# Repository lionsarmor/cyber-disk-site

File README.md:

# RODDY Cyber Disk inspector

Website: http://disk.roddy.world/

GitHub Pages: https://lionsarmor.github.io/cyber-disk-site/ (redirects to the custom domain).

Hardware R3 publication: five routed PCBs with actual RODDY silkscreen, separate KiCad/schematic/Gerber downloads, supplier-grouped BOM, Drive R5 mechanism and External Case R4 with Daughterboard R3. The development repository remains private.

Saved-file ERC, DRC and independent pin-map checks pass with zero unrouted connections. These are prototype files: printed/powered sample qualification and real-host emulation testing remain required. Firmware is unchanged in this hardware publication.

GitHub Actions deploys `site/` to GitHub Pages on each push to main. DNS: CNAME `disk` points to `lionsarmor.github.io`. All asset URLs are relative. Obsolete generated geometry has been removed from the current deployment; historical revisions remain in Git.

Start with `?model=pcb%2Fdock&view=b&v=hardware-r3` for the branded PCB underside, `?model=drive%2Fmotion&v=hardware-r3` for the mechanism, or `?model=external%2Fservice&v=hardware-r3` for internal wiring. Board files are at `boards.html`; verification details are at `electrical.html`.

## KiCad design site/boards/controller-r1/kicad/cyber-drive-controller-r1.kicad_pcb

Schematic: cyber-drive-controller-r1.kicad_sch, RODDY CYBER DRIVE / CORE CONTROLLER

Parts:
A1: PICO 2 SC1632 SOCKETED; Controller_A1
C1: 47uF 16V; Controller_C1
C2: 100nF 50V; Controller_C2
C3: 100nF 50V; Controller_C3
C5: 100nF 50V; Controller_C5
C6: 22uF 16V / OUTPUT; Controller_C6
C7: 100nF 50V; Controller_C7
C9: 1uF 50V X7R; Controller_C9
C10: 22nF AUDIO LP1; Controller_C10
C11: 22nF AUDIO LP2; Controller_C11
C12: 100nF AUDIO COUPLING; Controller_C12
C13: 100uF 16V / SPEAKER DC BLOCK; Controller_C13
C14: 47uF 16V / AMP RESERVOIR; Controller_C14
C15: 100nF AMP DECOUPLING; Controller_C15
C16: 100nF AUDIO STABILITY; Controller_C16
C17: 22uF 16V / AMP BYPASS; Controller_C17
D1: 1N5819 / USB BACKFEED BLOCK; Controller_D1
F1: 2A FAST / LOW DROP; Controller_F1
J1: 34-PIN PC FLOPPY; Controller_J1
J2: FLOPPY POWER 5V GND GND 12V; Controller_J2
J3: 1725708 / CONTACT WIRES 1 TO 7; Controller_J3
J4: DOCK LINK 3V3 UART; Controller_J4
J5: 3V3 OUT / INTERLOCK RETURN; Controller_J5
J6: SPEAKER 8 OHM / + GND; Controller_J6
Q1: IRLZ44N / HARD DISCHARGE; Controller_Q1
Q2: TN0702 / ARM PERMISSION; Controller_Q2
Q3: TN0702 / INTERLOCK PERMISSION; Controller_Q3
Q4: TN0702 / FDD INDEX; Controller_Q4
Q5: TN0702 / FDD TRK0; Controller_Q5
Q6: TN0702 / FDD WP; Controller_Q6
Q7: TN0702 / FDD RDATA; Controller_Q7
Q8: TN0702 / FDD CHANGE; Controller_Q8
Q9: SUP53P06 / MEDIA INPUT CUT; Controller_Q9
Q10: TN0702 / OE ARM; Controller_Q10
Q11: TN0702 / OE INTERLOCK; Controller_Q11
R1: 10k SPI CS DEFAULT; Controller_R1
R2: 10k MEDIA ERROR PULLUP; Controller_R2
R4: 15k 1%; Controller_R4
R5: 10k 1%; Controller_R5
R6: 68R FAILSAFE BLEED; Controller_R6
R7: 680R DEFAULT OFF; Controller_R7
R8: 2R2 DISCHARGE; Controller_R8
R9: 10k MISO DEFAULT; Controller_R9
R10: 1 OHM CAP ESR; Controller_R10
R11: 2k2 ARM GATE; Controller_R11
R12: 2k2 INTERLOCK GATE; Controller_R12
R13: 10k OE DEFAULT OFF; Controller_R13
R14: 47k AUDIO ATTENUATOR; Controller_R14
R15: 2k2 AUDIO BIAS; Controller_R15
R16: 2k2 AUDIO FILTER; Controller_R16
R17: 10R AUDIO STABILITY; Controller_R17
RN1: 8x10k BUSSED / COMMON PIN1; Controller_RN1
RN2: 8x10k BUSSED / COMMON PIN1; Controller_RN2
RN3: 8x1k BUSSED / COMMON GND; Controller_RN3
U1: SN74LVC245AN / 5V-TOL INPUT; Controller_U1
U2: SN74LVC245AN / 5V-TOL INPUT; Controller_U2
U4: SN74LVC245AN / SWITCHED MEDIA ISOLATION; Controller_U4
U6: LP2951ACN / SWITCHED 3V1 100mA; Controller_U6
U7: LM386N-1 / SAMPLE AUDIO; Controller_U7

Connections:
AMP_BYPASS: C17.1 (AMP_BYPASS), U7.7 (AMP_BYPASS)
AMP_OUT: C13.1 (AMP_OUT), C16.1 (AMP_OUT), U7.5 (AMP_OUT)
ARM_BASE: Q2.2 (ARM_BASE), Q10.2 (ARM_BASE), R11.2 (ARM_BASE)
ASSERT_CHANGE: A1.21 (ASSERT_CHANGE), Q8.2 (ASSERT_CHANGE), RN3.6 (ASSERT_CHANGE)
ASSERT_INDEX: A1.16 (ASSERT_INDEX), Q4.2 (ASSERT_INDEX), RN3.2 (ASSERT_INDEX)
ASSERT_RDATA: A1.20 (ASSERT_RDATA), Q7.2 (ASSERT_RDATA), RN3.5 (ASSERT_RDATA)
ASSERT_TRK0: A1.17 (ASSERT_TRK0), Q5.2 (ASSERT_TRK0), RN3.3 (ASSERT_TRK0)
ASSERT_WP: A1.19 (ASSERT_WP), Q6.2 (ASSERT_WP), RN3.4 (ASSERT_WP)
AUDIO_IN: C12.2 (AUDIO_IN), U7.3 (AUDIO_IN)
AUDIO_LP1: C10.1 (AUDIO_LP1), R14.2 (AUDIO_LP1), R15.1 (AUDIO_LP1), R16.1 (AUDIO_LP1)
AUDIO_LP2: C11.1 (AUDIO_LP2), C12.1 (AUDIO_LP2), R16.2 (AUDIO_LP2)
AUDIO_PWM: A1.32 (AUDIO_PWM), R14.1 (AUDIO_PWM)
AUDIO_ZOBEL: C16.2 (AUDIO_ZOBEL), R17.1 (AUDIO_ZOBEL)
DISCHARGE_C: Q1.2 (DISCHARGE_C), R8.2 (DISCHARGE_C)
DOCK_BUSY: A1.34 (DOCK_BUSY), J4.5 (DOCK_BUSY)
DOCK_RX: A1.2 (DOCK_RX), U2.16 (DOCK_RX)
DOCK_RX_RAW: J4.4 (DOCK_RX_RAW), RN3.7 (DOCK_RX_RAW), U2.4 (DOCK_RX_RAW)
DOCK_TX: A1.1 (DOCK_TX), J4.3 (DOCK_TX)
FDD_CHANGE_N: J1.34 (FDD_CHANGE_N), Q8.3 (FDD_CHANGE_N)
FDD_DENSEL: J1.2 (FDD_DENSEL), RN2.3 (FDD_DENSEL), U2.3 (FDD_DENSEL)
FDD_DIR_N: J1.18 (FDD_DIR_N), RN1.6 (FDD_DIR_N), U1.6 (FDD_DIR_N)
FDD_DS_A_N: J1.14 (FDD_DS_A_N), RN1.4 (FDD_DS_A_N), U1.4 (FDD_DS_A_N)
FDD_DS_B_N: J1.12 (FDD_DS_B_N), RN1.3 (FDD_DS_B_N), U1.3 (FDD_DS_B_N)
FDD_HEAD_N: J1.32 (FDD_HEAD_N), RN2.2 (FDD_HEAD_N), U2.2 (FDD_HEAD_N)
FDD_INDEX_N: J1.8 (FDD_INDEX_N), Q4.3 (FDD_INDEX_N)
FDD_MOTOR_A_N: J1.10 (FDD_MOTOR_A_N), RN1.2 (FDD_MOTOR_A_N), U1.2 (FDD_MOTOR_A_N)
FDD_MOTOR_B_N: J1.16 (FDD_MOTOR_B_N), RN1.5 (FDD_MOTOR_B_N), U1.5 (FDD_MOTOR_B_N)
FDD_RDATA_N: J1.30 (FDD_RDATA_N), Q7.3 (FDD_RDATA_N)
FDD_STEP_N: J1.20 (FDD_STEP_N), RN1.7 (FDD_STEP_N), U1.7 (FDD_STEP_N)
FDD_TRK0_N: J1.26 (FDD_TRK0_N), Q5.3 (FDD_TRK0_N)
FDD_WDATA_N: J1.22 (FDD_WDATA_N), RN1.8 (FDD_WDATA_N), U1.8 (FDD_WDATA_N)
FDD_WGATE_N: J1.24 (FDD_WGATE_N), RN1.9 (FDD_WGATE_N), U1.9 (FDD_WGATE_N)
FDD_WP_N: J1.28 (FDD_WP_N), Q6.3 (FDD_WP_N)
GND: A1.3 (GND), A1.8 (GND), A1.13 (GND), A1.18 (GND), A1.23 (GND), A1.28 (GND), A1.33 (GND), A1.38 (GND), C1.2 (GND), C2.2 (GND), C3.2 (GND), C5.2 (GND), C7.2 (GND), C9.2 (GND), C10.2 (GND), C11.2 (GND), C14.2 (GND), C15.2 (GND), C17.2 (GND), J1.1 (GND), J1.3 (GND), J1.5 (GND), J1.7 (GND), J1.9 (GND), J1.11 (GND), J1.13 (GND), J1.15 (GND), J1.17 (GND), J1.19 (GND), J1.21 (GND), J1.23 (GND), J1.25 (GND), J1.27 (GND), J1.29 (GND), J1.31 (GND), J1.33 (GND), J2.2 (GND), J2.3 (GND), J3.1 (GND), J4.1 (GND), J4.8 (GND), J6.2 (GND), Q1.3 (GND), Q3.1 (GND), Q4.1 (GND), Q5.1 (GND), Q6.1 (GND), Q7.1 (GND), Q8.1 (GND), Q11.1 (GND), R5.2 (GND), R6.2 (GND), R9.2 (GND), R10.2 (GND), R15.2 (GND), R17.2 (GND), RN3.1 (GND), U1.10 (GND), U1.19 (GND), U2.5 (GND), U2.6 (GND), U2.7 (GND), U2.8 (GND), U2.9 (GND), U2.10 (GND), U2.19 (GND), U4.6 (GND), U4.7 (GND), U4.8 (GND), U4.9 (GND), U4.10 (GND), U6.4 (GND), U7.2 (GND), U7.4 (GND)
INTERLOCK_OK: A1.29 (INTERLOCK_OK), J5.2 (INTERLOCK_OK), R12.1 (INTERLOCK_OK), RN3.9 (INTERLOCK_OK)
LOCK_BASE: Q3.2 (LOCK_BASE), Q11.2 (LOCK_BASE), R12.2 (LOCK_BASE)
MCU_DENSEL: A1.15 (MCU_DENSEL), U2.17 (MCU_DENSEL)
MCU_DIR_N: A1.9 (MCU_DIR_N), U1.14 (MCU_DIR_N)
MCU_DS_A_N: A1.6 (MCU_DS_A_N), U1.16 (MCU_DS_A_N)
MCU_DS_B_N: A1.5 (MCU_DS_B_N), U1.17 (MCU_DS_B_N)
MCU_HEAD_N: A1.14 (MCU_HEAD_N), U2.18 (MCU_HEAD_N)
MCU_MOTOR_A_N: A1.4 (MCU_MOTOR_A_N), U1.18 (MCU_MOTOR_A_N)
MCU_MOTOR_B_N: A1.7 (MCU_MOTOR_B_N), U1.15 (MCU_MOTOR_B_N)
MCU_STEP_N: A1.10 (MCU_STEP_N), U1.13 (MCU_STEP_N)
MCU_WDATA_N: A1.11 (MCU_WDATA_N), U1.12 (MCU_WDATA_N)
MCU_WGATE_N: A1.12 (MCU_WGATE_N), U1.11 (MCU_WGATE_N)
MEDIA_3V3: C6.1 (MEDIA_3V3), C7.1 (MEDIA_3V3), J3.2 (MEDIA_3V3), R4.1 (MEDIA_3V3), R6.1 (MEDIA_3V3), R8.1 (MEDIA_3V3), R13.1 (MEDIA_3V3), U4.1 (MEDIA_3V3), U4.20 (MEDIA_3V3), U6.1 (MEDIA_3V3)
MEDIA_ARM: A1.27 (MEDIA_ARM), R11.1 (MEDIA_ARM), RN3.8 (MEDIA_ARM)
MEDIA_CAP_RETURN: C6.2 (MEDIA_CAP_RETURN), R10.1 (MEDIA_CAP_RETURN)
MEDIA_CS_N: J3.3 (MEDIA_CS_N), U4.18 (MEDIA_CS_N)
MEDIA_ERROR_N: A1.31 (MEDIA_ERROR_N), R2.2 (MEDIA_ERROR_N), U6.5 (MEDIA_ERROR_N)
MEDIA_FB: R4.2 (MEDIA_FB), R5.1 (MEDIA_FB), U6.7 (MEDIA_FB)
MEDIA_MISO: J3.6 (MEDIA_MISO), U4.5 (MEDIA_MISO)
MEDIA_MOSI: J3.5 (MEDIA_MOSI), U4.16 (MEDIA_MOSI)
MEDIA_OE_N: Q10.3 (MEDIA_OE_N), R13.2 (MEDIA_OE_N), U4.19 (MEDIA_OE_N)
MEDIA_OFF: Q1.1 (MEDIA_OFF), Q2.3 (MEDIA_OFF), Q9.1 (MEDIA_OFF), R7.2 (MEDIA_OFF), U6.3 (MEDIA_OFF)
MEDIA_SCK: J3.4 (MEDIA_SCK), U4.17 (MEDIA_SCK)
OE_MID: Q10.1 (OE_MID), Q11.3 (OE_MID)
PERMISSION_MID: Q2.1 (PERMISSION_MID), Q3.3 (PERMISSION_MID)
SPI_CS_N: A1.22 (SPI_CS_N), R1.2 (SPI_CS_N), U4.2 (SPI_CS_N)
SPI_MISO: A1.26 (SPI_MISO), R9.1 (SPI_MISO), U4.15 (SPI_MISO)
SPI_MOSI: A1.25 (SPI_MOSI), U4.4 (SPI_MOSI)
SPI_SCK: A1.24 (SPI_SCK), U4.3 (SPI_SCK)
SPK_PLUS: C13.2 (SPK_PLUS), J6.1 (SPK_PLUS)
V3V3: A1.36 (V3V3), C2.1 (V3V3), C3.1 (V3V3), C5.1 (V3V3), J4.7 (V3V3), J5.1 (V3V3), R1.1 (V3V3), R2.1 (V3V3), U1.1 (V3V3), U1.20 (V3V3), U2.1 (V3V3), U2.20 (V3V3)
V5: C1.1 (V5), C9.1 (V5), C14.1 (V5), C15.1 (V5), D1.2 (V5), F1.2 (V5), J4.2 (V5), Q9.3 (V5), R7.1 (V5), RN1.1 (V5), RN2.1 (V5), U7.6 (V5)
V5_IN: F1.1 (V5_IN), J2.1 (V5_IN)
V5_MEDIA: Q9.2 (V5_MEDIA), U6.8 (V5_MEDIA)
VSYS: A1.39 (VSYS), D1.1 (VSYS)

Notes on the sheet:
R1: Standard IBM-PC 34-pin FDD rear interface; cable twist handled by firmware selection. 5V inputs use 5.5V-tolerant LVC245 at 3.3V. Outputs are TN0702 open drain; ASSERT=1 pulls cable LOW. J3 is the isolated seven-wire contact output. J5 series seat-NO/eject-NC loop MUST open before disk motion. 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

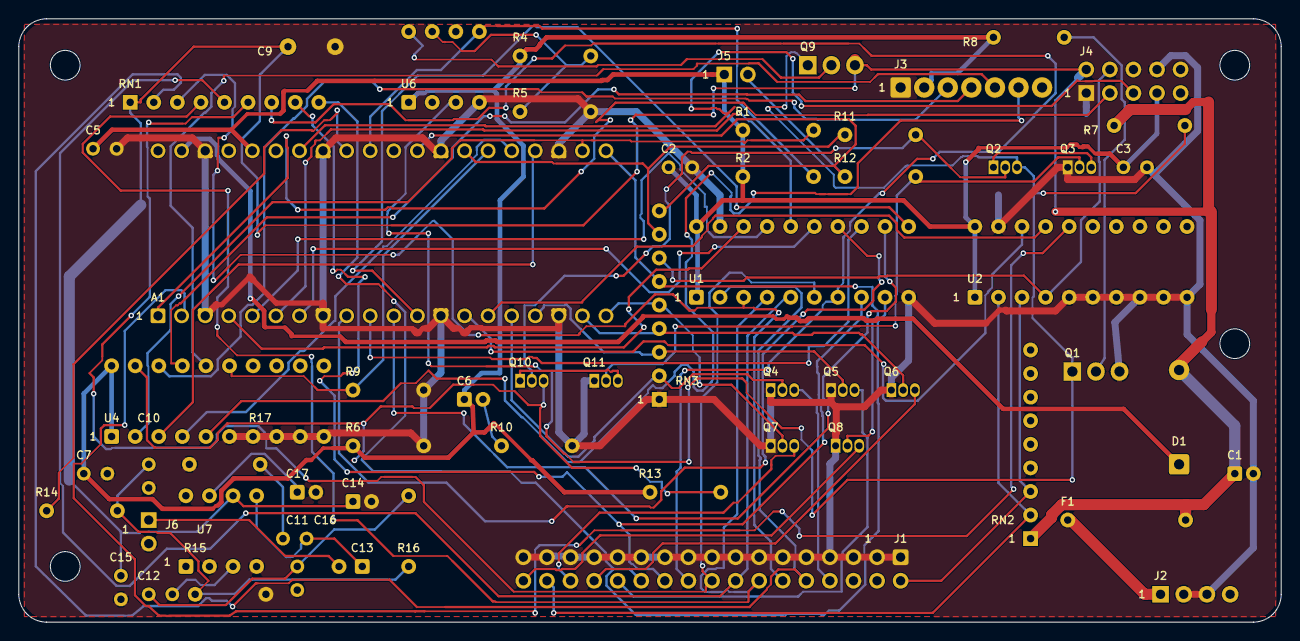
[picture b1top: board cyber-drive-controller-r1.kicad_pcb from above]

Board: 2 copper layers, 136.0 x 65.0 mm, 63 parts (0 on the bottom side), 69 nets.

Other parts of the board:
H1: MountingHole_3.2mm_M3; Controller_H1
H2: MountingHole_3.2mm_M3; Controller_H2
H3: MountingHole_3.2mm_M3; Controller_H3
H4: MountingHole_3.2mm_M3; Controller_H4

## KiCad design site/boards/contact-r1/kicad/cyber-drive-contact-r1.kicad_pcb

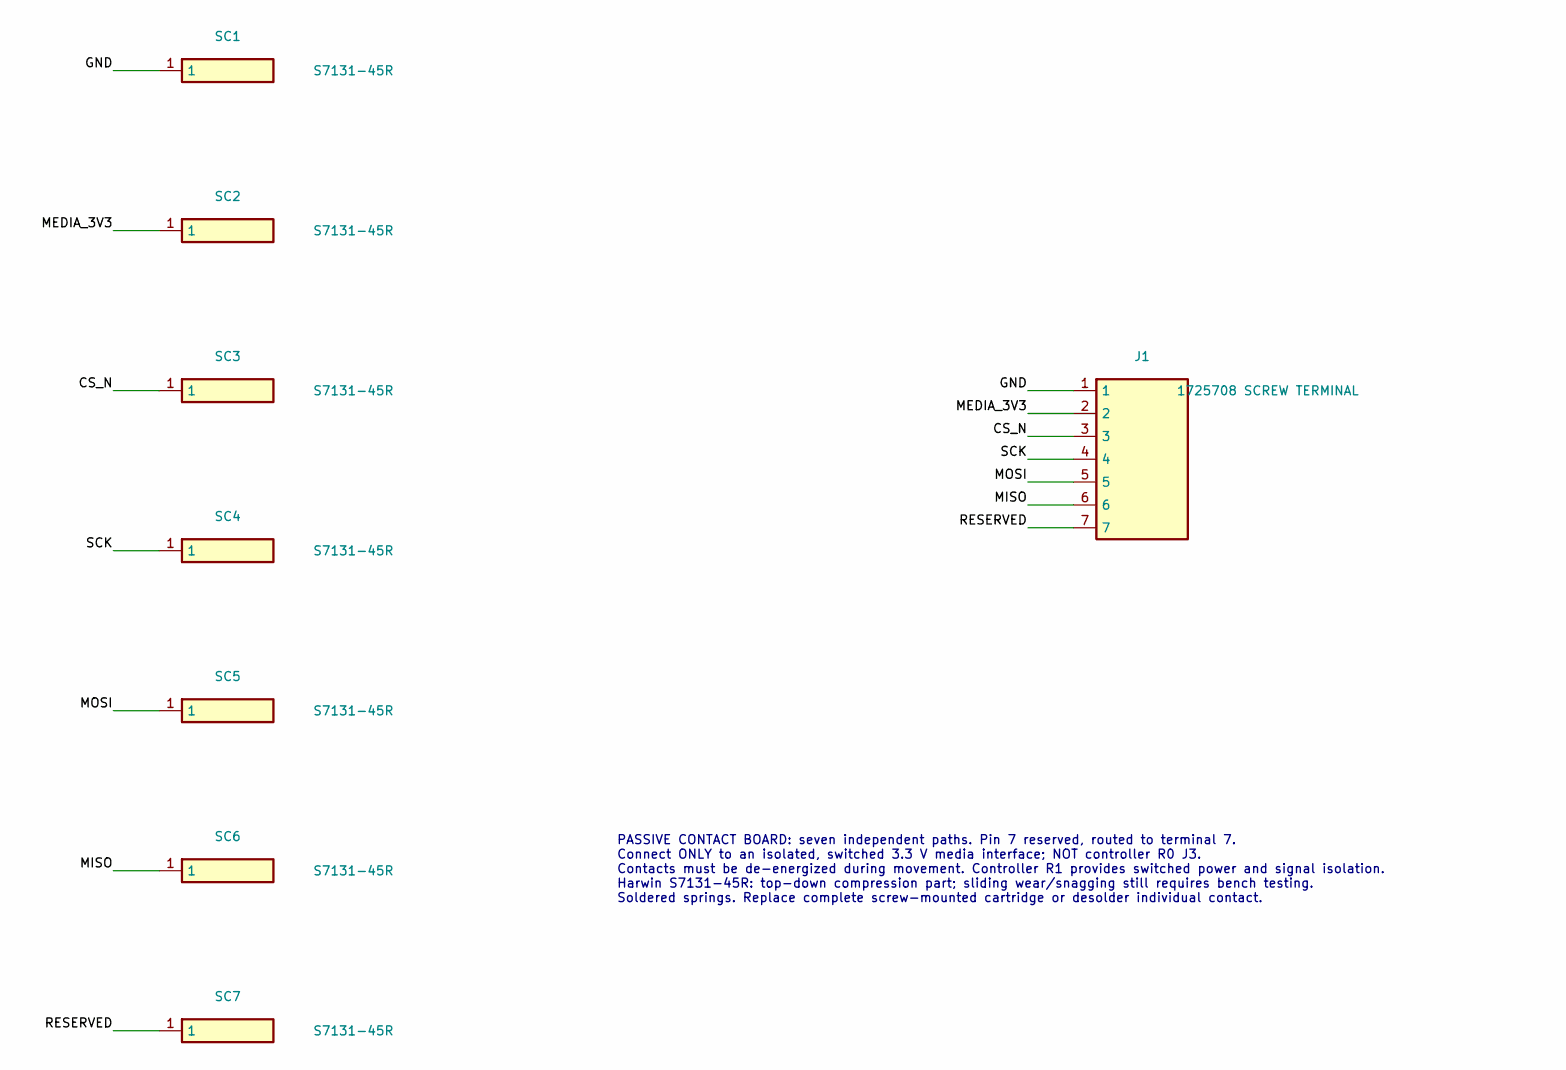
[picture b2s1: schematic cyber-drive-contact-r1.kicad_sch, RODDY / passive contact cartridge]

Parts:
J1: 1725708 SCREW TERMINAL; Terminal7_Phoenix1725708
SC1, SC2, SC3, SC4, SC5, SC6, SC7: S7131-45R; Contact__Harwin_S7131-45R

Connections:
/CS_N: J1.3, SC3.1
/GND: J1.1, SC1.1
/MEDIA_3V3: J1.2, SC2.1
/MISO: J1.6, SC6.1
/MOSI: J1.5, SC5.1
/RESERVED: J1.7, SC7.1
/SCK: J1.4, SC4.1

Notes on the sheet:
PASSIVE CONTACT BOARD: seven independent paths. Pin 7 reserved, routed to terminal 7. Connect ONLY to an isolated, switched 3.3 V media interface; NOT controller R0 J3. Contacts must be de-energized during movement. Controller R1 provides switched power and signal isolation. Harwin S7131-45R: top-d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

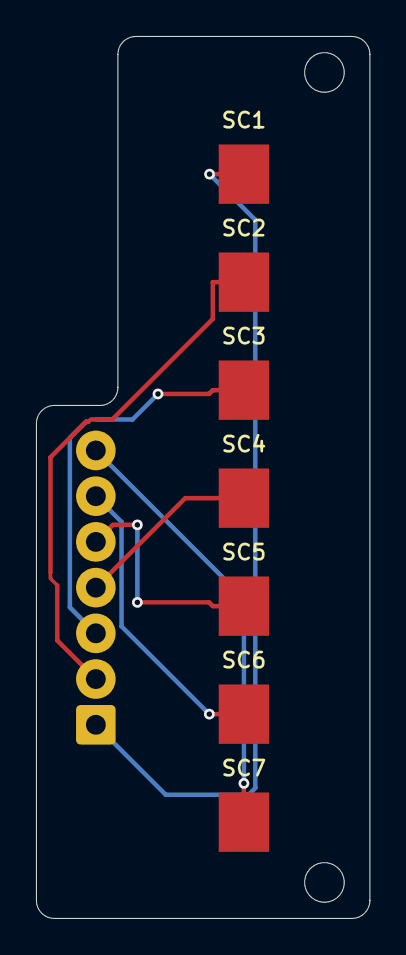
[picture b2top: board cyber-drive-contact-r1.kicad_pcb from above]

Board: 2 copper layers, 18.5 x 49.0 mm, 10 parts (1 on the bottom side), 7 nets.

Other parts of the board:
H1: M2 NPTH; BoardMount_H1
H2: M2 NPTH; BoardMount_H2

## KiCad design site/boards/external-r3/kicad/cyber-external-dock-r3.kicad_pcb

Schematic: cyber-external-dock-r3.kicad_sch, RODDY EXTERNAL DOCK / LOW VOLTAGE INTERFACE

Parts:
A1: Pico 2 / internal USB jumper; Module__RaspberryPi_Pico_Common_THT
C1, C2, C3, C4: 1uF 50V nonpolar; Dock__C330_P5.08
C5, C7, C8, C9, C10, C11: 100nF 50V; Dock__C315_P2.54
C12: 100uF 16V; Capacitor_THT__CP_Radial_D6.3mm_P2.50mm
C13: 1000uF 10V LED bulk; Capacitor_THT__CP_Radial_D10.0mm_P5.00mm
D1: 1N5819 / VSYS feed only; Diode_THT__D_DO-41_SOD81_P10.16mm_Horizontal
F1: 2A fast / input; Resistor_THT__R_Axial_DIN0309_L9.0mm_D3.2mm_P12.70mm_Horizo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
J1: IEC / Switchcraft sequential pin numbers; Dock__DIN_61PC6F
J2: DE9 female DCE; Dock__DE9_09661527612
J3: ACCESSORY SPI / 3V3 SIGNALS / NO POWER; Dock__WR_BHD_61202021721
J4: CORE J4 / SIGNALS ONLY; Connector_IDC__IDC-Header_2x05_P2.54mm_Vertical
J5: 5V ONLY / CENTRE +; Dock__BarrelJack_PJ102AH_2024
J6: CORE BERG 5V / 12V NC; Connector_PinHeader_2.54mm__PinHeader_1x02_P2.54mm_Vertical
J7: LED STRIP 5V / 0.2A MAX; Connector_PinHeader_2.54mm__PinHeader_1x03_P2.54mm_Vertical
J8: PIEZO / 1k LIMITED; Connector_PinHeader_2.54mm__PinHeader_1x02_P2.54mm_Vertical
J9: USB-B / HOST INPUT; Dock__USB_B_61729
J10: INTERNAL ONLY / TO PICO; Connector_USB__USB_A_Molex_67643_Horizontal
Q1: SUP53P06-20-E3 / reverse polarity; Package_TO_SOT_THT__TO-220-3_Vertical
Q2: TN0702 / IEC CLK; Package_TO_SOT_THT__TO-92_Inline
Q3: TN0702 / IEC DATA; Package_TO_SOT_THT__TO-92_Inline
Q4: TN0702 / IEC SRQ; Package_TO_SOT_THT__TO-92_Inline
R1, R2, R3, R5, R6: 10k; Resistor_THT__R_Axial_DIN0207_L6.3mm_D2.5mm_P7.62mm_Horizon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
R4: 330; Resistor_THT__R_Axial_DIN0207_L6.3mm_D2.5mm_P7.62mm_Horizon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
R7, R8: 4k7 MARK / DEASSERT; Resistor_THT__R_Axial_DIN0207_L6.3mm_D2.5mm_P7.62mm_Horizon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
R9, R10: 10k UNPOWERED SERIAL DEFAULT; Resistor_THT__R_Axial_DIN0207_L6.3mm_D2.5mm_P7.62mm_Horizon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
R11: 1k PIEZO CURRENT LIMIT; Resistor_THT__R_Axial_DIN0207_L6.3mm_D2.5mm_P7.62mm_Horizon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
RN1: 5 x 47k IEC DISCONNECTED LOW; Resistor_THT__R_Array_SIP6
RN2: 3 x 1k GATE boot pulldown; Resistor_THT__R_Array_SIP4
RN3: 8 x 4k7 INPUT DEFAULTS; Resistor_THT__R_Array_SIP9
U1, U4, U5: SN74LVC245AN; Package_DIP__DIP-20_W7.62mm
U3: MAX232N / 5V RS232; Package_DIP__DIP-16_W7.62mm
U6: SN74AHCT125N / LED + serial TX; Package_DIP__DIP-14_W7.62mm

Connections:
ACC_CS_N: J3.9 (ACC_CS_N), R2.1 (ACC_CS_N), U4.4 (ACC_CS_N)
ACC_CS_S: A1.22 (ACC_CS_S), U4.16 (ACC_CS_S)
ACC_DETECT_N: J3.13 (ACC_DETECT_N), R3.1 (ACC_DETECT_N), U4.5 (ACC_DETECT_N)
ACC_DETECT_S: A1.20 (ACC_DETECT_S), U4.15 (ACC_DETECT_S)
ACC_MISO: J3.7 (ACC_MISO), U5.18 (ACC_MISO)
ACC_MISO_DRV: A1.25 (ACC_MISO_DRV), RN3.7 (ACC_MISO_DRV), U5.2 (ACC_MISO_DRV)
ACC_MOSI: J3.5 (ACC_MOSI), RN3.3 (ACC_MOSI), U4.3 (ACC_MOSI)
ACC_MOSI_S: A1.21 (ACC_MOSI_S), U4.17 (ACC_MOSI_S)
ACC_OE_N: A1.27 (ACC_OE_N), R1.1 (ACC_OE_N), U5.19 (ACC_OE_N)
ACC_READY: J3.11 (ACC_READY), U5.17 (ACC_READY)
ACC_READY_DRV: A1.26 (ACC_READY_DRV), RN3.8 (ACC_READY_DRV), U5.3 (ACC_READY_DRV)
ACC_SCK: J3.3 (ACC_SCK), RN3.2 (ACC_SCK), U4.2 (ACC_SCK)
ACC_SCK_S: A1.24 (ACC_SCK_S), U4.18 (ACC_SCK_S)
ASSERT_CLK: A1.10 (ASSERT_CLK), Q2.2 (ASSERT_CLK), RN2.2 (ASSERT_CLK)
ASSERT_DATA: A1.16 (ASSERT_DATA), Q3.2 (ASSERT_DATA), RN2.3 (ASSERT_DATA)
ASSERT_SRQ: A1.17 (ASSERT_SRQ), Q4.2 (ASSERT_SRQ), RN2.4 (ASSERT_SRQ)
AUDIO_OUT: J8.1 (AUDIO_OUT), R11.2 (AUDIO_OUT)
AUDIO_PWM: A1.31 (AUDIO_PWM), R11.1 (AUDIO_PWM)
CORE_BUSY: A1.19 (CORE_BUSY), U4.13 (CORE_BUSY)
CORE_BUSY_RAW: J4.5 (CORE_BUSY_RAW), RN3.5 (CORE_BUSY_RAW), U4.7 (CORE_BUSY_RAW)
CORE_LED_RAW: J4.6 (CORE_LED_RAW), RN3.6 (CORE_LED_RAW), U4.8 (CORE_LED_RAW)
CORE_LED_S: A1.32 (CORE_LED_S), U4.12 (CORE_LED_S)
CORE_RX: A1.2 (CORE_RX), U4.14 (CORE_RX)
CORE_RX_RAW: J4.3 (CORE_RX_RAW), RN3.4 (CORE_RX_RAW), U4.6 (CORE_RX_RAW)
CORE_TX: A1.1 (CORE_TX), J4.4 (CORE_TX)
CP1N: C1.2 (CP1N), U3.3 (CP1N)
CP1P: C1.1 (CP1P), U3.1 (CP1P)
CP2N: C2.2 (CP2N), U3.5 (CP2N)
CP2P: C2.1 (CP2P), U3.4 (CP2P)
GND: A1.3 (GND), A1.8 (GND), A1.13 (GND), A1.18 (GND), A1.23 (GND), A1.28 (GND), A1.33 (GND), A1.38 (GND), C3.2 (GND), C4.1 (GND), C5.2 (GND), C7.2 (GND), C8.2 (GND), C9.2 (GND), C10.2 (GND), C11.2 (GND), C12.2 (GND), C13.2 (GND), J1.3 (GND), J1.SH (GND), J2.5 (GND), J2.SH (GND), J3.1 (GND), J3.2 (GND), J3.4 (GND), J3.6 (GND), J3.8 (GND), J3.10 (GND), J3.12 (GND), J3.14 (GND), J3.16 (GND), J3.18 (GND), J3.20 (GND), J4.1 (GND), J4.8 (GND), J5.2 (GND), J6.2 (GND), J7.3 (GND), J8.2 (GND), J9.4 (GND), J9.SH (GND), J10.4 (GND), J10.SH (GND), Q1.1 (GND), Q2.1 (GND), Q3.1 (GND), Q4.1 (GND), R6.2 (GND), R9.2 (GND), R10.2 (GND), RN1.1 (GND), RN2.1 (GND), RN3.1 (GND), U1.10 (GND), U1.19 (GND), U3.15 (GND), U4.9 (GND), U4.10 (GND), U4.19 (GND), U5.4 (GND), U5.5 (GND), U5.6 (GND), U5.7 (GND), U5.8 (GND), U5.9 (GND), U5.10 (GND), U6.1 (GND), U6.4 (GND), U6.7 (GND), U6.10 (GND), U6.12 (GND)
IEC_ATN: J1.5 (IEC_ATN), RN1.2 (IEC_ATN), U1.2 (IEC_ATN)
IEC_ATN_S: A1.4 (IEC_ATN_S), U1.18 (IEC_ATN_S)
IEC_CLK: J1.2 (IEC_CLK), Q2.3 (IEC_CLK), RN1.3 (IEC_CLK), U1.3 (IEC_CLK)
IEC_CLK_S: A1.5 (IEC_CLK_S), U1.17 (IEC_CLK_S)
IEC_DATA: J1.4 (IEC_DATA), Q3.3 (IEC_DATA), RN1.4 (IEC_DATA), U1.4 (IEC_DATA)
IEC_DATA_S: A1.6 (IEC_DATA_S), U1.16 (IEC_DATA_S)
IEC_RESET: J1.6 (IEC_RESET), RN1.6 (IEC_RESET), U1.6 (IEC_RESET)
IEC_RESET_S: A1.9 (IEC_RESET_S), U1.14 (IEC_RESET_S)
IEC_SRQ: J1.1 (IEC_SRQ), Q4.3 (IEC_SRQ), RN1.5 (IEC_SRQ), U1.5 (IEC_SRQ)
IEC_SRQ_S: A1.7 (IEC_SRQ_S), U1.15 (IEC_SRQ_S)
LED_DATA: A1.29 (LED_DATA), RN3.9 (LED_DATA), U6.2 (LED_DATA)
LED_OUT: J7.2 (LED_OUT), R4.2 (LED_OUT)
LED_OUT_RAW: R4.1 (LED_OUT_RAW), U6.3 (LED_OUT_RAW)
POWER_PRESENT: A1.34 (POWER_PRESENT), U1.11 (POWER_PRESENT)
POWER_SENSE: R5.2 (POWER_SENSE), R6.1 (POWER_SENSE), U1.9 (POWER_SENSE)
RS_CTS_5V: R10.1 (RS_CTS_5V), U1.8 (RS_CTS_5V), U3.9 (RS_CTS_5V)
RS_CTS_OUT: J2.8 (RS_CTS_OUT), U3.7 (RS_CTS_OUT)
RS_RTS_IN: J2.7 (RS_RTS_IN), U3.8 (RS_RTS_IN)
RS_RX_5V: R9.1 (RS_RX_5V), U1.7 (RS_RX_5V), U3.12 (RS_RX_5V)
RS_RX_IN: J2.3 (RS_RX_IN), U3.13 (RS_RX_IN)
RS_TX_OUT: J2.2 (RS_TX_OUT), U3.14 (RS_TX_OUT)
RS_VMINUS: C4.2 (RS_VMINUS), U3.6 (RS_VMINUS)
RS_VPLUS: C3.1 (RS_VPLUS), U3.2 (RS_VPLUS)
SERIAL_CTS: A1.14 (SERIAL_CTS), U1.12 (SERIAL_CTS)
SERIAL_RTS: A1.15 (SERIAL_RTS), R8.2 (SERIAL_RTS), U6.9 (SERIAL_RTS)
SERIAL_RTS_5V: U3.10 (SERIAL_RTS_5V), U6.8 (SERIAL_RTS_5V)
SERIAL_RX: A1.12 (SERIAL_RX), U1.13 (SERIAL_RX)
SERIAL_TX: A1.11 (SERIAL_TX), R7.2 (SERIAL_TX), U6.5 (SERIAL_TX)
SERIAL_TX_5V: U3.11 (SERIAL_TX_5V), U6.6 (SERIAL_TX_5V)
USB_DM: J9.2 (USB_DM), J10.2 (USB_DM)
USB_DP: J9.3 (USB_DP), J10.3 (USB_DP)
USB_VBUS: J9.1 (USB_VBUS), J10.1 (USB_VBUS)
V3V3: A1.36 (V3V3), C5.1 (V3V3), C8.1 (V3V3), C9.1 (V3V3), C11.1 (V3V3), R1.2 (V3V3), R2.2 (V3V3), R3.2 (V3V3), R7.1 (V3V3), R8.1 (V3V3), U1.1 (V3V3), U1.20 (V3V3), U4.1 (V3V3), U4.20 (V3V3), U5.1 (V3V3), U5.20 (V3V3)
V5: C7.1 (V5), C10.1 (V5), C12.1 (V5), C13.1 (V5), D1.2 (V5), J6.1 (V5), J7.1 (V5), Q1.3 (V5), R5.1 (V5), U3.16 (V5), U6.13 (V5), U6.14 (V5)
V5_FUSED: F1.2 (V5_FUSED), Q1.2 (V5_FUSED)
V5_RAW: F1.1 (V5_RAW), J5.1 (V5_RAW)
VSYS: A1.39 (VSYS), D1.1 (VSYS)

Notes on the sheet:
5V regulated centre-positive barrel only. Q1 protects reverse polarity, NOT overvoltage. J9 USB-B to J10 internal USB-A and Adafruit898 A/micro-B jumper to Pico. USB_VBUS NOT tied to V5. Core J4 pins2 and7 NC. Core power uses separate 5V Berg cable;12V position NC. Accessory is custom3V3 SPI only, 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

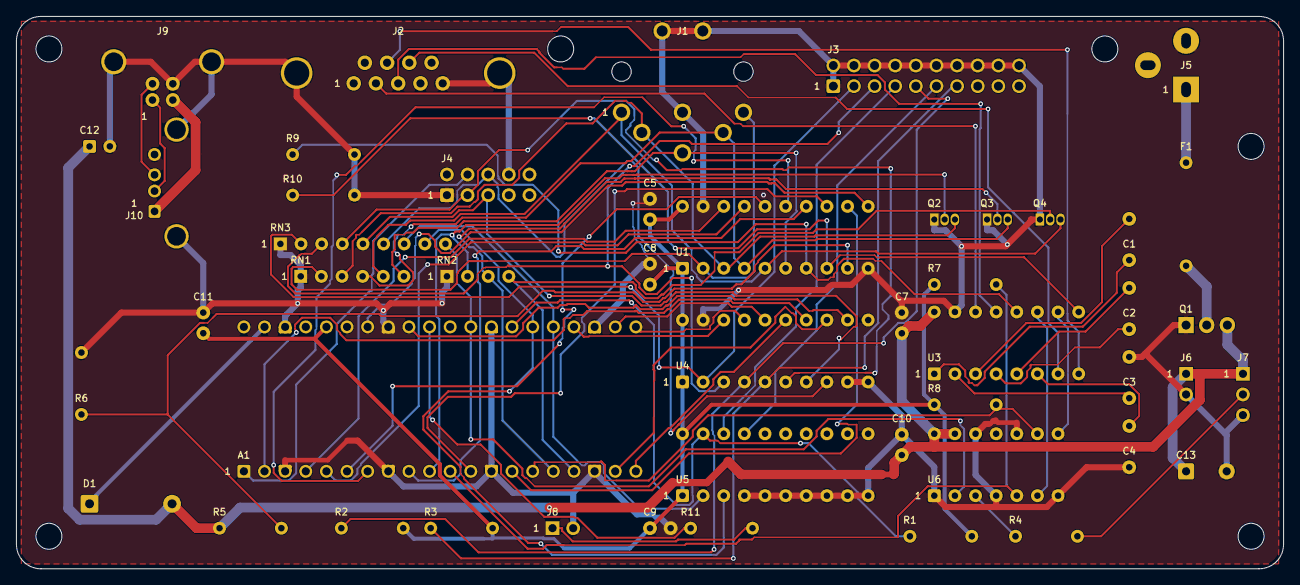
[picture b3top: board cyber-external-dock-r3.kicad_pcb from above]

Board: 2 copper layers, 156.0 x 68.0 mm, 54 parts (0 on the bottom side), 67 nets.

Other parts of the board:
H1, H2, H3, H4, H5, H6: MountingHole_3.2mm_M3

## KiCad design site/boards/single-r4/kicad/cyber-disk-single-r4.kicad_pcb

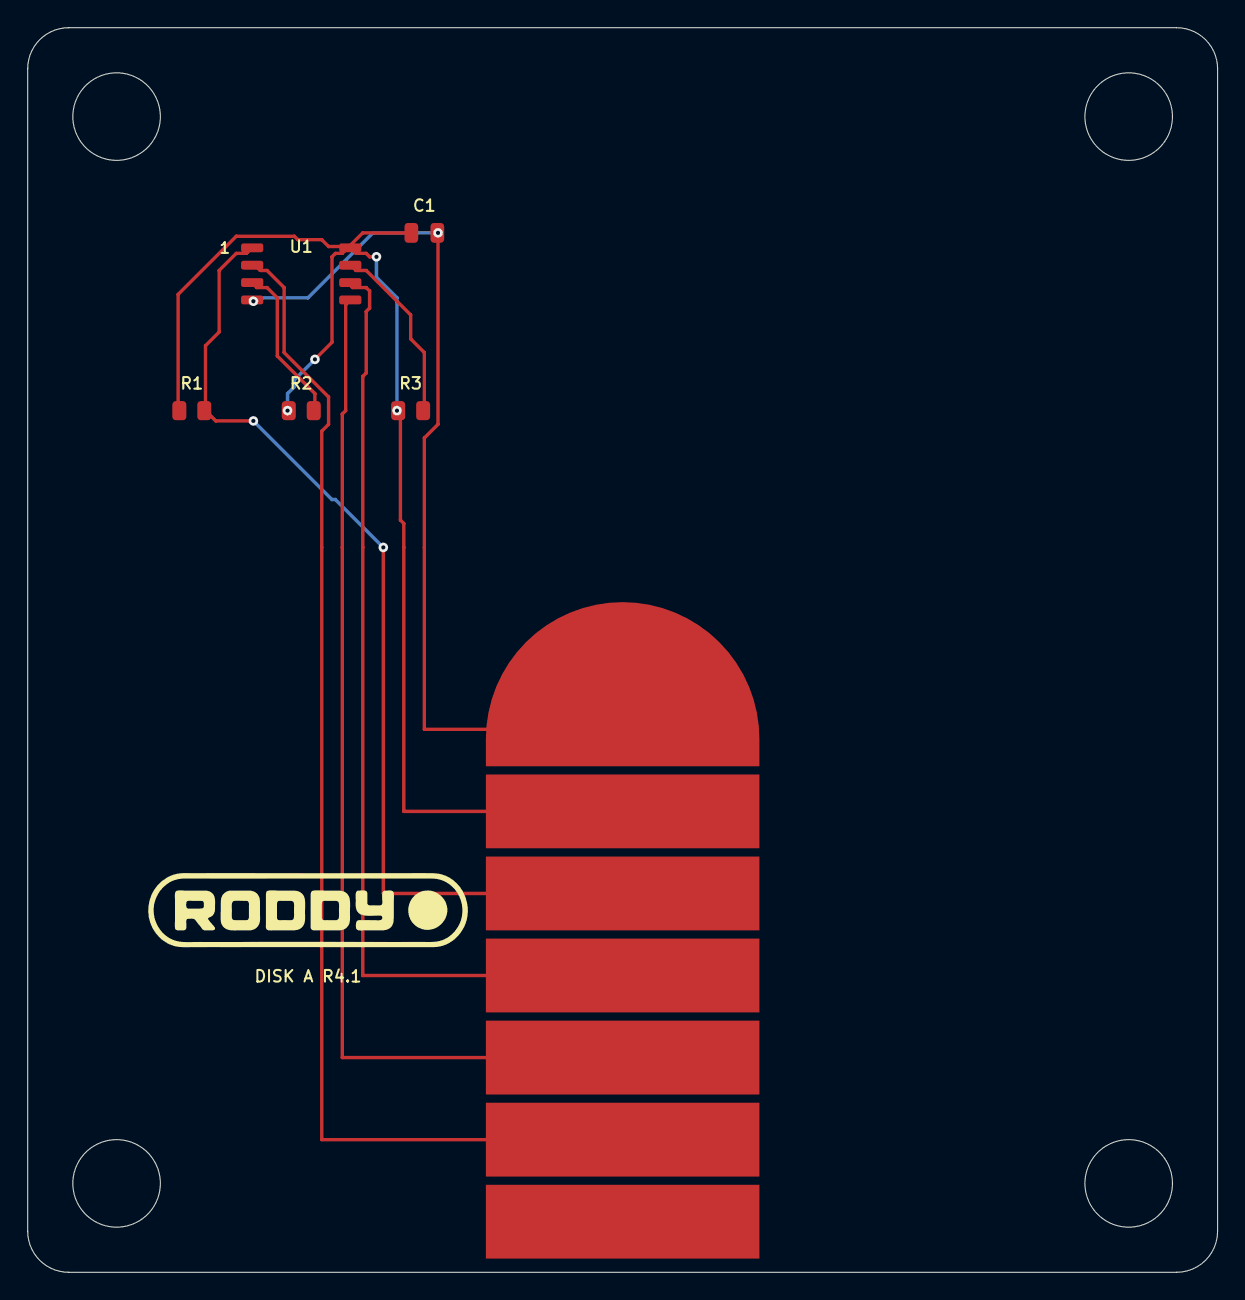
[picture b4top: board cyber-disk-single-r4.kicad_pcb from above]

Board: 2 copper layers, 87.0 x 91.0 mm, 10 parts (0 on the bottom side), 8 nets.

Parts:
C1: 100nF; Capacitor_SMD__C_0805_2012Metric
H1: STRUCTURAL_POST_CLEARANCE_6.4; BoardMount_H1
H2: STRUCTURAL_POST_CLEARANCE_6.4; BoardMount_H2
H3: STRUCTURAL_POST_CLEARANCE_6.4; BoardMount_H3
H4: STRUCTURAL_POST_CLEARANCE_6.4; BoardMount_H4
J1: Contact7_F; Roddy__Contact7_F
R1, R2, R3: 10k; Resistor_SMD__R_0805_2012Metric
U1: MX25L3233FM2I-08G-TR; Package_SO__SOIC-8_5.3x5.3mm_P1.27mm

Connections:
A_CLK: J1.4, U1.6
A_CS: J1.3, R1.2, U1.1
A_GND: C1.2, J1.1, U1.4
A_HOLD: R3.2, U1.7
A_MISO: J1.6, U1.2
A_MOSI: J1.5, U1.5
A_VCC: C1.1, J1.2, R1.1, R2.1, R3.1, U1.8
A_WP: R2.2, U1.3

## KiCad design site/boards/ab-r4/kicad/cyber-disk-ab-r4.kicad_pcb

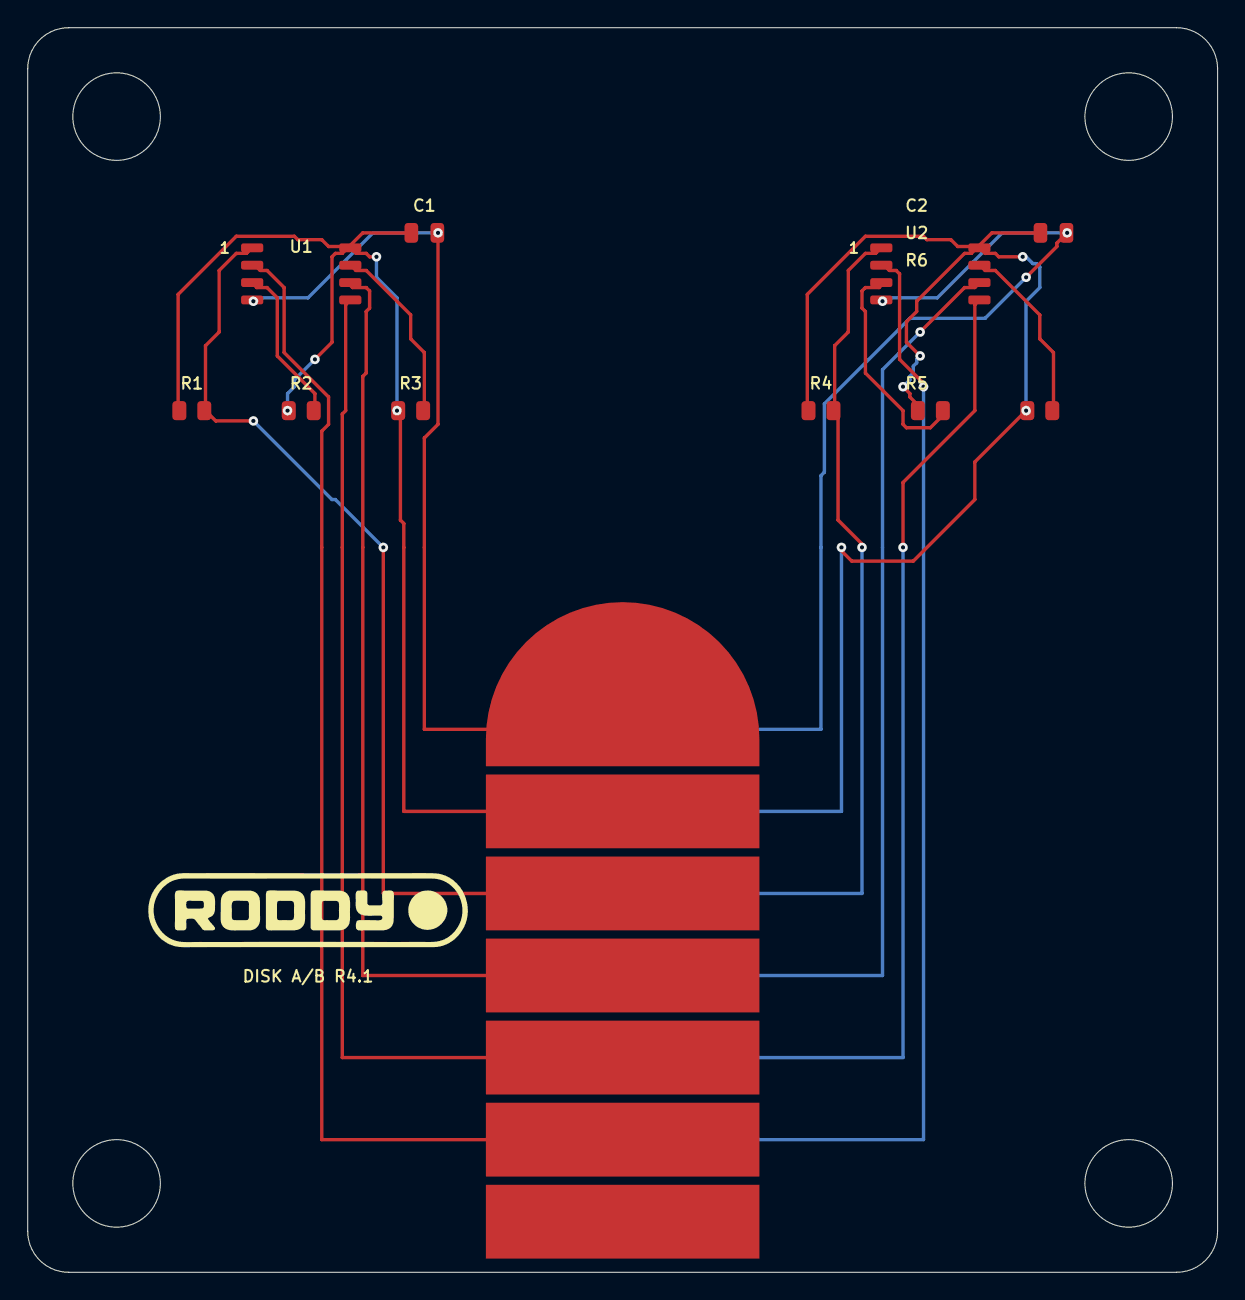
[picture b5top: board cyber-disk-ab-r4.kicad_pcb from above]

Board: 2 copper layers, 87.0 x 91.0 mm, 16 parts (1 on the bottom side), 16 nets.

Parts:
C1, C2: 100nF; Capacitor_SMD__C_0805_2012Metric
H1: STRUCTURAL_POST_CLEARANCE_6.4; BoardMount_H1
H2: STRUCTURAL_POST_CLEARANCE_6.4; BoardMount_H2
H3: STRUCTURAL_POST_CLEARANCE_6.4; BoardMount_H3
H4: STRUCTURAL_POST_CLEARANCE_6.4; BoardMount_H4
J1: Contact7_F; Roddy__Contact7_F
J2: Contact7_B; Roddy__Contact7_B
R1, R2, R3, R4, R5, R6: 10k; Resistor_SMD__R_0805_2012Metric
U1, U2: MX25L3233FM2I-08G-TR; Package_SO__SOIC-8_5.3x5.3mm_P1.27mm

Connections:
A_CLK: J1.4, U1.6
A_CS: J1.3, R1.2, U1.1
A_GND: C1.2, J1.1, U1.4
A_HOLD: R3.2, U1.7
A_MISO: J1.6, U1.2
A_MOSI: J1.5, U1.5
A_VCC: C1.1, J1.2, R1.1, R2.1, R3.1, U1.8
A_WP: R2.2, U1.3
B_CLK: J2.4, U2.6
B_CS: J2.3, R4.2, U2.1
B_GND: C2.2, J2.1, U2.4
B_HOLD: R6.2, U2.7
B_MISO: J2.6, U2.2
B_MOSI: J2.5, U2.5
B_VCC: C2.1, J2.2, R4.1, R5.1, R6.1, U2.8
B_WP: R5.2, U2.3
